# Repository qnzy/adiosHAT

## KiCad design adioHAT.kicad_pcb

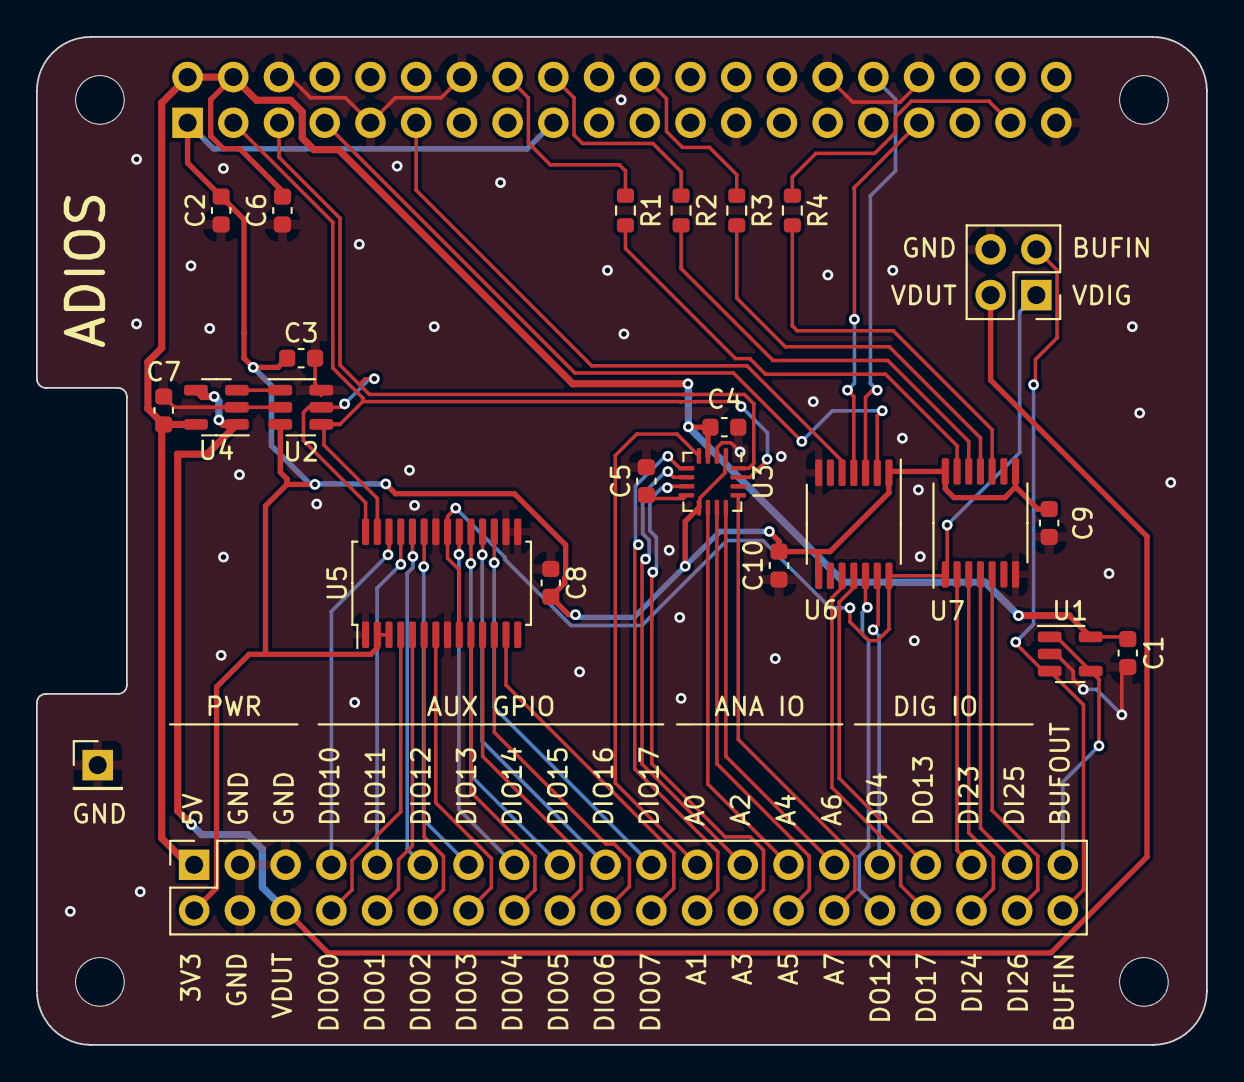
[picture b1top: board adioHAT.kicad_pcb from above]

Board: 2 copper layers, 65.0 x 56.0 mm, 29 parts (1 on the bottom side), 55 nets.

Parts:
C1, C2, C3, C4, C5, C6, C7, C8, C9, C10: 100n; C_0603_1608Metric
J1: Conn_01x01; PinHeader_1x01_P2.54mm_Vertical
J2: Conn_02x02_Odd_Even; PinHeader_2x02_P2.54mm_Vertical
J3, J4: Conn_02x20_Odd_Even; PinSocket_2x20_P2.54mm_Vertical
MH1, MH2, MH3, MH4: MountingHole_2.7mm_M2.5
R1, R2, R3, R4: 100; R_0603_1608Metric
U1: AD8603; TSOT-23-5
U2: DAC7571; SOT-23-6
U3: AD5593R; LFCSP-16-3x3mm_P0.5mm.3x1.3mm
U4: LM7321; SOT-23-5
U5: PCA9575D; TSSOP-28_4.4x9.7mm_P0.65mm
U6, U7: TXU0104; TSSOP-14_4.4x5mm_P0.65mm

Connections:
+3V3: C2.2, C3.2, C8.2, C9.2, C10.2, J3.1, J3.17, J4.2, U2.3 (VDD), U3.1 (~RESET), U3.9 (V_{LOGIC}), U5.2 (VDD), U5.3 (~RESET), U6.1 (VCCA), U6.8 (OE), U7.8 (OE), U7.14 (VCCB)
+5V: C1.2, C4.2, C6.2, C7.2, J3.2, J3.4, J4.1, U1.5 (V+), U3.3 (V_{DD}), U4.5 (V+)
/A0: J4.23, U3.4 (IO0)
/A1: J4.24, U3.5 (IO1)
/A2: J4.25, U3.6 (IO2)
/A3: J4.26, U3.7 (IO3)
/A4: J4.27, U3.10 (IO4)
/A5: J4.28, U3.11 (IO5)
/A6: J4.29, U3.12 (IO6)
/A7: J4.30, U3.13 (IO7)
/BUFIN: J2.3, J4.40, U1.3 (+)
/BUFOUT: J4.39, U1.1, U1.4 (-)
/DIO00: J4.8, U5.4 (P0_0)
/DIO01: J4.10, U5.5 (P0_1)
/DIO02: J4.12, U5.6 (P0_2)
/DIO03: J4.14, U5.7 (P0_3)
/DIO04: J4.16, U5.10 (P0_4)
/DIO05: J4.18, U5.11 (P0_5)
/DIO06: J4.20, U5.12 (P0_6)
/DIO07: J4.22, U5.13 (P0_7)
/DIO10: J4.7, U5.26 (P1_0)
/DIO11: J4.9, U5.25 (P1_1)
/DIO12: J4.11, U5.24 (P1_2)
/DIO13: J4.13, U5.23 (P1_3)
/DIO14: J4.15, U5.20 (P1_4)
/DIO15: J4.17, U5.19 (P1_5)
/DIO16: J4.19, U5.18 (P1_6)
/DIO17: J4.21, U5.17 (P1_7)
/GPCLK0: J3.7, U6.2 (A1)
/GPCLK0_DUT: J4.31, U6.13 (B1Y)
/GPIO17: J3.11, U6.5 (A4)
/GPIO17_DUT: J4.34, U6.10 (B4Y)
/GPIO23: J3.16, R1.1
/GPIO23_DUT: J4.35, U7.2 (A1)
/GPIO24: J3.18, R2.1
/GPIO24_DUT: J4.36, U7.3 (A2)
/GPIO25: J3.22, R3.1
/GPIO25_DUT: J4.37, U7.4 (A3)
/GPIO26: J3.37, R4.1
/GPIO26_DUT: J4.38, U7.5 (A4)
/PWM0: J3.32, U6.3 (A2)
/PWM0_DUT: J4.32, U6.12 (B2Y)
/PWM1: J3.33, U6.4 (A3)
/PWM1_DUT: J4.33, U6.11 (B3Y)
/SCL: J3.5, U2.5 (SCL), U3.16 (SCL), U5.28 (SCL)
/SDA: J3.3, U2.4 (SDA), U3.15 (SDA), U5.27 (SDA)
/VDUT: J2.2, J4.6, U4.1 (OUT), U4.4 (IN-)
/VGPIO: J2.1, U5.9 (VDDIO0), U5.21 (VDDIO1), U6.14 (VCCB), U7.1 (VCCA)
GND: C1.1, C2.1, C3.1, C4.1, C5.1, C6.1, C7.1, C8.1, C9.1, C10.1, J1.1, J2.4, J3.6, J3.9, J3.14, J3.20, J3.25, J3.30, J3.34, J3.39, J4.3, J4.4, J4.5, U1.2 (V-), U2.2 (GND), U2.6 (A0), U3.2 (A0), U3.14 (GND), U4.2 (V-), U5.1 (A0), U5.8 (A1), U5.15 (A2), U5.16 (VSS), U5.22 (A3), U6.7 (GND), U7.7 (GND)
unnamed: U2.1 (VOUT), U4.3 (IN+)
unnamed: C5.2, U3.8 (V_{REF})
unnamed: R1.2, U7.13 (B1Y)
unnamed: R2.2, U7.12 (B2Y)
unnamed: R3.2, U7.11 (B3Y)
unnamed: R4.2, U7.10 (B4Y)

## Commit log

2023-07-14 exchanged DAC IC
2023-07-21 improved silkscreen text
2023-08-13 fixed i2c connections for ad5593
2023-08-13 moved some elements inwards to increase border clearance
2023-08-19 added comment on VDIG
